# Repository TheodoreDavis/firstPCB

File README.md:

# firstPCB
files for my first real pcb
Using https://www.linkedin.com/learning/learning-pcb-design-with-eagle/develop-the-board-layout as a guide.

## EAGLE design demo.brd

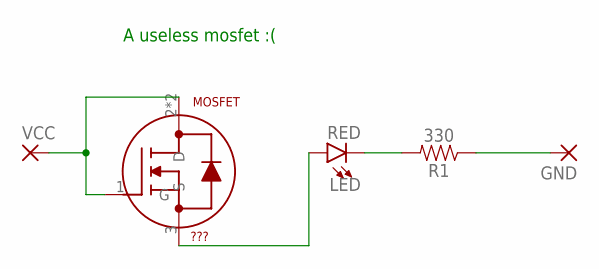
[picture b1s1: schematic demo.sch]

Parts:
GND: SMD2; SMD1,27-2,54
LED: RED; LED-1206
MOSFET: ???; CSTM_MOSFET
R1: 330; 1206
VCC: SMD2; SMD1,27-2,54

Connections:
unnamed: GND.1, R1.1
unnamed: LED.C, R1.2
unnamed: MOSFET.1 (G), MOSFET.2 (D), MOSFET.2B (D), VCC.1
unnamed: LED.A, MOSFET.3 (S)

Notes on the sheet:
A useless mosfet :(

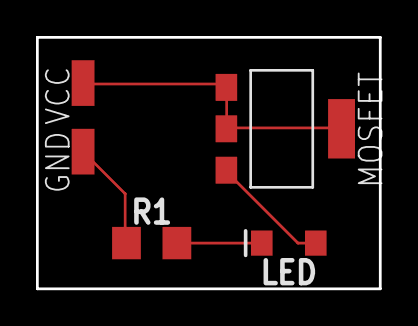
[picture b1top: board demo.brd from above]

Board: 2 copper layers, 19.1 x 14.0 mm, 5 parts (0 on the bottom side), 4 nets.

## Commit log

2021-05-20 led schematic build
2021-05-20 messing around with brd
2021-05-21 Added custom part

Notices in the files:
parts and their libraries:
SparkFun-LED: Licensing: Creative Commons ShareAlike 4.0 International - https://creativecommons.org/licenses/by-sa/4.0
